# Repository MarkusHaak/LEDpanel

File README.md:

# LEDpanel
A multifunctional, bluetooth controlled LED panel for illuminating 96-well microtiter plates containing biological or chemical samples. The first version of this hardware was developed as part of the iGEM project from team Bielefeld CeBiTec 2017. For a detailed description of this first model and its applications in our project, see the [Hardware page](2017.igem.org/Team:Bielefeld-CeBiTec/Hardware) of our project wiki.

## Disclaimer

The hardware described on this github repository is still in prototype phase and both software and hardware may contain design faults. Furthermore, I do not take any responsibility and I am not liable for any damage that is caused by handling of electrical components or devices based on designs, instructions and information in this repository.

## Some Hints for Assembly

This repository is new and there is a lack of documentation. Until I find the time to write a comprehensive instruction for assembly and usage, the following hints are intended to give some orientation.

* In principal, any LEDs can be mounted on the LED panel. The constant current flowing through the LEDs is adjustable with potentiometers on the PCB itself. The LED panel is designed to be configurable to either control the current of all LEDs with a single potentiometer, or two groups of LEDs with an individual potentiometer for each group. Therefore, it is possible to mount two different groups of LEDs on the LED panel. In any case, I highly recommend to adapt the footprint in the PCB design files according to the instructions in the LED's technical sheets.

* Please adapt the file "model_slim_microtiter_adapter.stl" to fit the micro titer plates that are used in your laboratory.

* The parts list is outdated and is probably missing some required parts. Anyways, it might give some orientation in choosing the right parts.

* The LED panel requires two different voltages supplied over a micro usb cable: 3.3 V for the micro controller and logic, and a seperate LED supply voltage that should be at least 0.4 volts above the supply voltage of the LEDs in use. I used two LM2596 based DC-DC voltage regulator boards in a seperate 3d printed case (voltage_regulators_case.stl) to supply the required voltages from a standard 5V DC mains adapter with a barrel connector.

* The LED panel is intended to be controlled over bluetooth via an Android application. Nevertheless, some gpio pins of the teensy are traced to the side of the PCB for optional soldering of pin headers to the PCB that allow the connection of a small LCD screen and a rotary encoder to control basic functionalities of the LED panel. If this is intended, the Arduino code will probably need to be revised. In addition, the 3d printed case needs to be modified accordingly to create space for the display and the rotary encoder.

* The supplied .stl files are solely for illumination of micro titer plates from beneath. For illumination from above a plate, a different 3d printed microtiter adapter needs to be designed.

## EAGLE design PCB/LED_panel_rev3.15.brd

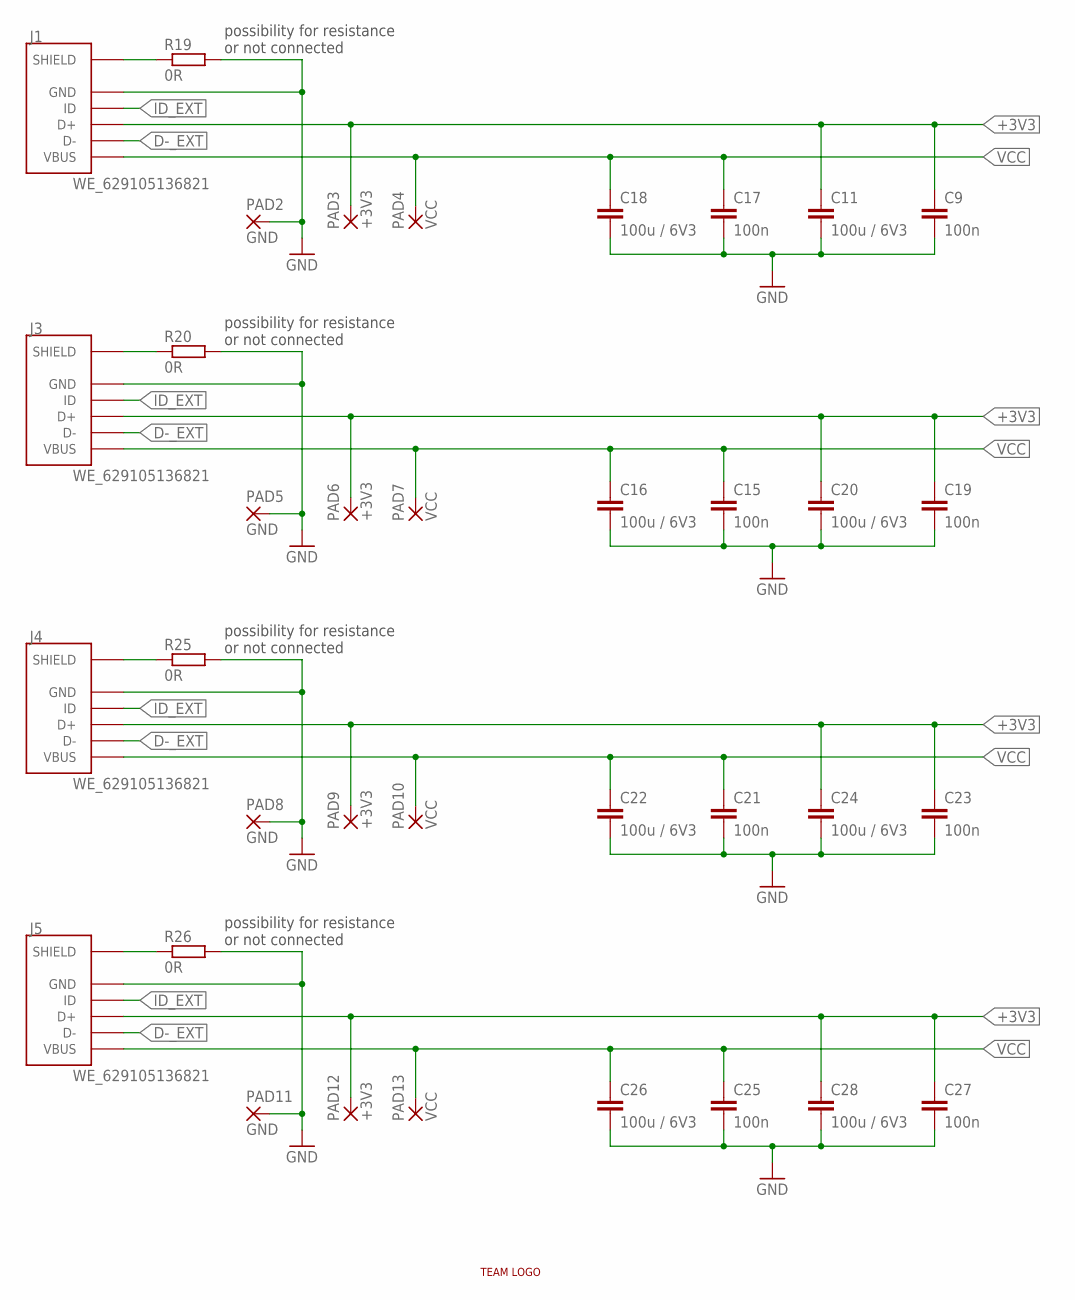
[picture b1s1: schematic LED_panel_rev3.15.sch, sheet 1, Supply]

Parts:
C9, C15, C17, C19, C21, C23, C25, C27: 100n; C1206K
C11, C16, C18, C20, C22, C24, C26, C28: 100u / 6V3; C1206K
J1, J3, J4, J5: WE_629105136821; 629105136821
PAD2, PAD5, PAD8, PAD11: GND; 2,54/1,0
PAD3, PAD6, PAD9, PAD12: +3V3; 2,54/1,0
PAD4, PAD7, PAD10, PAD13: VCC; 2,54/1,0
R19, R20, R25, R26: 0R; R1206
U$99: LOGO_RESTRICT

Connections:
+3V3: C9.1, C11.1, C19.1, C20.1, C23.1, C24.1, C27.1, C28.1, J1.3 (D+), J3.3 (D+), J4.3 (D+), J5.3 (D+), PAD3.1, PAD6.1, PAD9.1, PAD12.1; also elsewhere on the board
D-_EXT: J1.2 (D-), J3.2 (D-), J4.2 (D-), J5.2 (D-); also elsewhere on the board
GND: C9.2, C11.2, C15.2, C16.2, C17.2, C18.2, C19.2, C20.2, C21.2, C22.2, C23.2, C24.2, C25.2, C26.2, C27.2, C28.2, J1.5 (GND), J3.5 (GND), J4.5 (GND), J5.5 (GND), PAD2.1, PAD5.1, PAD8.1, PAD11.1, R19.2, R20.2, R25.2, R26.2; also elsewhere on the board
ID_EXT: J1.4 (ID), J3.4 (ID), J4.4 (ID), J5.4 (ID); also elsewhere on the board
SHIELD1: J1.6 (SHIELD), J1.7 (SHIELD), J1.8 (SHIELD), J1.9 (SHIELD), R19.1
SHIELD3: J3.6 (SHIELD), J3.7 (SHIELD), J3.8 (SHIELD), J3.9 (SHIELD), R20.1
SHIELD4: J4.6 (SHIELD), J4.7 (SHIELD), J4.8 (SHIELD), J4.9 (SHIELD), R25.1
SHIELD5: J5.6 (SHIELD), J5.7 (SHIELD), J5.8 (SHIELD), J5.9 (SHIELD), R26.1
VCC: C15.1, C16.1, C17.1, C18.1, C21.1, C22.1, C25.1, C26.1, J1.1 (VBUS), J3.1 (VBUS), J4.1 (VBUS), J5.1 (VBUS), PAD4.1, PAD7.1, PAD10.1, PAD13.1; also elsewhere on the board

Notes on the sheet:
possibility for resistance or not connected

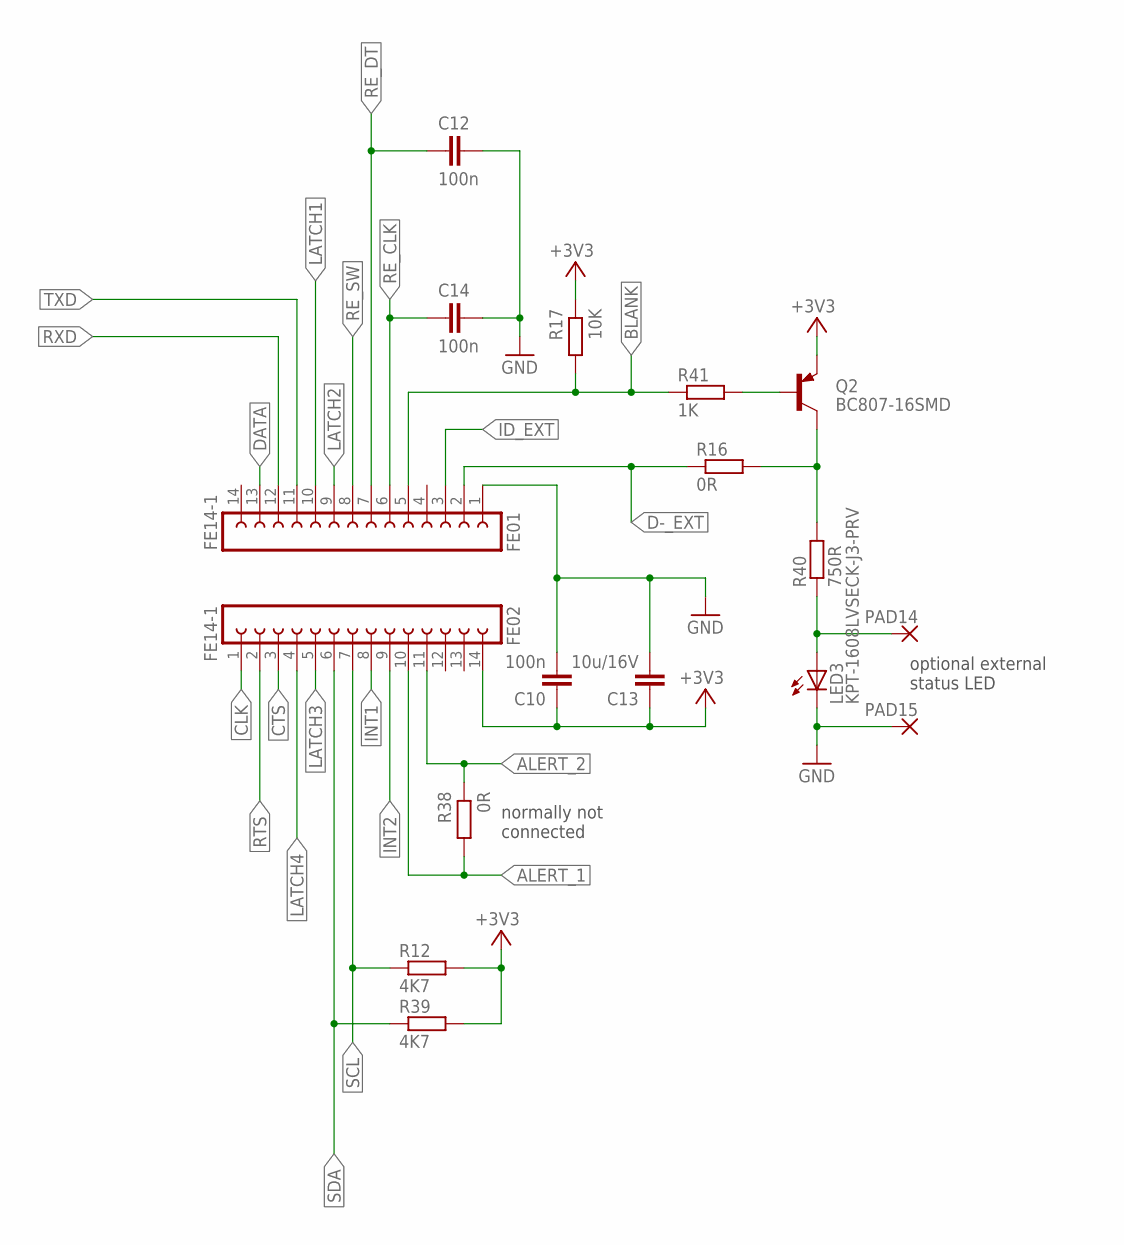
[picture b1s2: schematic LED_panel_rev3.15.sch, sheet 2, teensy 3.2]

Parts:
C10, C12, C14: 100n; C1206K
C13: 10u/16V; C1206K
FE01, FE02: FE14-1; FE14
LED3: KPT-1608LVSECK-J3-PRV; MH_KINGBRIGHT_1.6X0.8
PAD14, PAD15: 2,54/1,0
Q2: BC807-16SMD; SOT23-BEC
R12, R39: 4K7; R1206
R16, R38: 0R; R1206
R17: 10K; R1206
R40: 750R; R1206
R41: 1K; R1206

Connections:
+3V3: C10.1, C13.1, FE02.14, Q2.E, R12.2, R17.1, R39.2; also elsewhere on the board
ALERT_1: FE02.10, R38.2; also elsewhere on the board
ALERT_2: FE02.11, R38.1; also elsewhere on the board
BLANK: FE01.5, R17.2, R41.1; also elsewhere on the board
CLK: FE02.1; also elsewhere on the board
CTS: FE02.3; also elsewhere on the board
D-_EXT: FE01.2, R16.1; also elsewhere on the board
DATA: FE01.13; also elsewhere on the board
GND: C10.2, C12.1, C13.2, C14.1, FE01.1, LED3.C, PAD15.1; also elsewhere on the board
ID_EXT: FE01.3; also elsewhere on the board
INT1: FE02.8; also elsewhere on the board
INT2: FE02.9; also elsewhere on the board
LATCH1: FE01.10; also elsewhere on the board
LATCH2: FE01.9; also elsewhere on the board
LATCH3: FE02.5; also elsewhere on the board
LATCH4: FE02.4; also elsewhere on the board
unnamed: Q2.B, R41.2
unnamed: Q2.C, R16.2, R40.2
unnamed: LED3.A, PAD14.1, R40.1
RE_CLK: C14.2, FE01.6; also elsewhere on the board
RE_DT: C12.2, FE01.7; also elsewhere on the board
RE_SW: FE01.8; also elsewhere on the board
RTS: FE02.2; also elsewhere on the board
RXD: FE01.12; also elsewhere on the board
SCL: FE02.7, R12.1; also elsewhere on the board
SDA: FE02.6, R39.1; also elsewhere on the board
TXD: FE01.11; also elsewhere on the board

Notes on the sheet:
normally not connected
optional external status LED

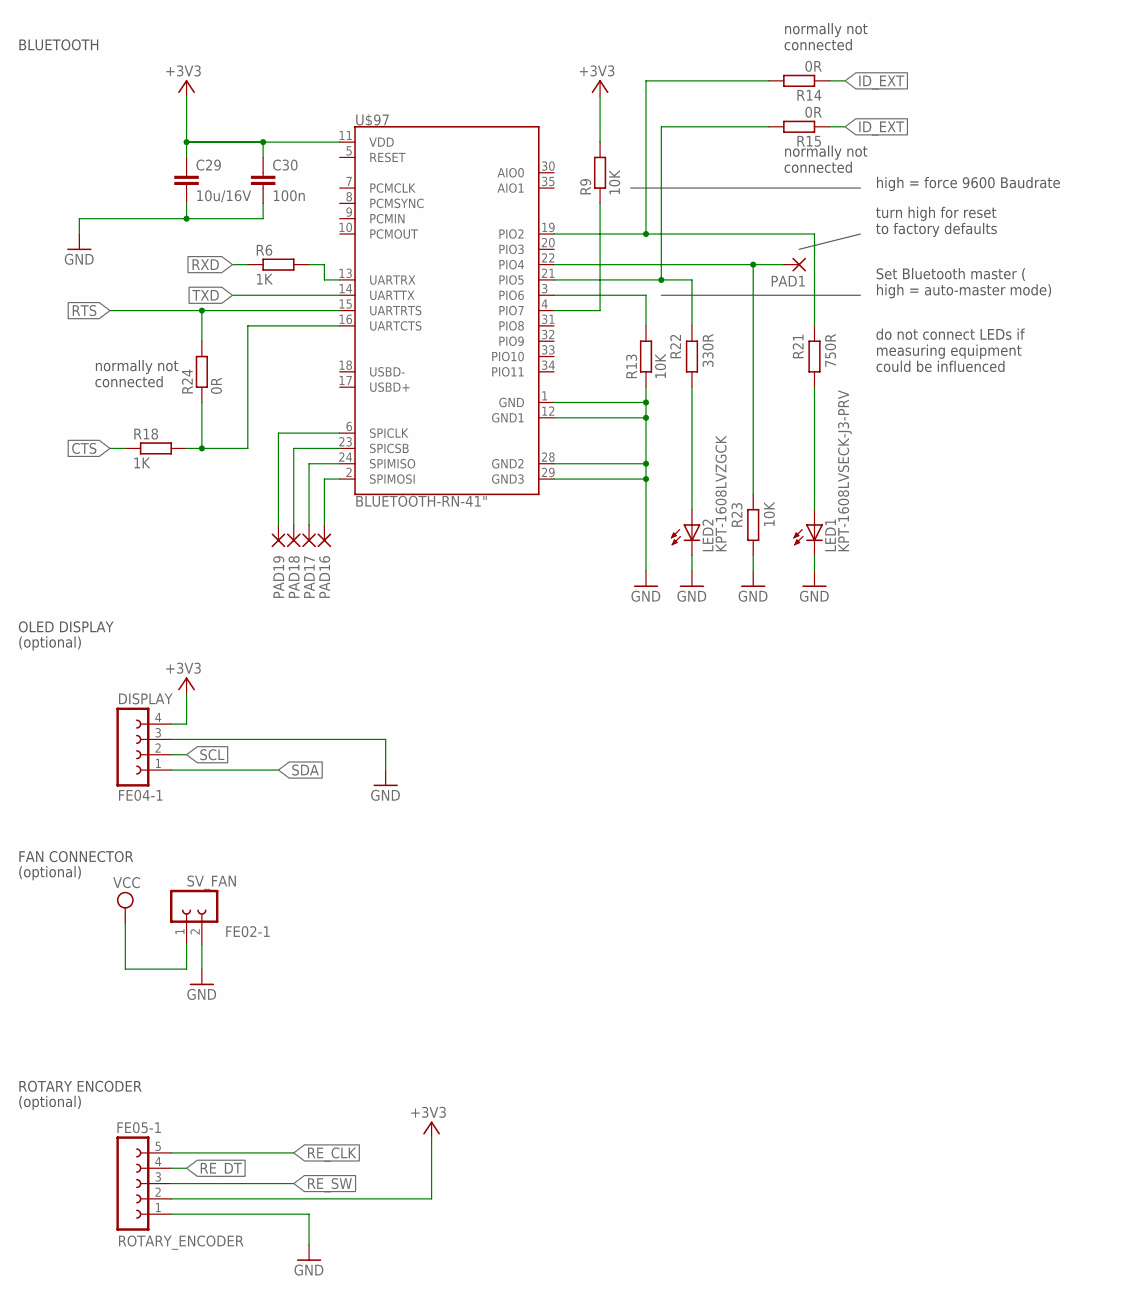
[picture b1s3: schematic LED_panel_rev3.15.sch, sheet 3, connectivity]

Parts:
C29: 10u/16V; C1206K
C30: 100n; C1206K
DISPLAY: FE04-1; FE04
LED1: KPT-1608LVSECK-J3-PRV; MH_KINGBRIGHT_1.6X0.8
LED2: KPT-1608LVZGCK; MH_KINGBRIGHT_1.6X0.8
PAD1, PAD16, PAD17, PAD18, PAD19: 2,54/1,0
R6, R18: 1K; R1206
R9, R13, R23: 10K; R1206
R14, R15, R24: 0R; R1206
R21: 750R; R1206
R22: 330R; R1206
ROTARY_ENCODER: FE05-1; FE05
SV_FAN: FE02-1; FE02
U$97: BLUETOOTH-RN-41"; RN41

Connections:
+3V3: C29.1, C30.1, DISPLAY.4, R9.2, ROTARY_ENCODER.2, U$97.11 (VDD); also elsewhere on the board
CTS: R18.1; also elsewhere on the board
GND: C29.2, C30.2, DISPLAY.3, LED1.C, LED2.C, R13.1, R23.2, ROTARY_ENCODER.1, SV_FAN.2, U$97.1 (GND), U$97.12 (GND1), U$97.28 (GND2), U$97.29 (GND3); also elsewhere on the board
ID_EXT: R14.1, R15.1; also elsewhere on the board
unnamed: R9.1, U$97.4 (PIO7)
unnamed: R13.2, U$97.3 (PIO6)
unnamed: R18.2, R24.1, U$97.16 (UARTCTS)
unnamed: PAD16.1, U$97.2 (SPIMOSI)
unnamed: PAD17.1, U$97.24 (SPIMISO)
unnamed: R6.2, U$97.13 (UARTRX)
unnamed: PAD18.1, U$97.23 (SPICSB)
unnamed: R15.2, R22.1, U$97.21 (PIO5)
unnamed: LED2.A, R22.2
unnamed: PAD19.1, U$97.6 (SPICLK)
unnamed: LED1.A, R21.2
unnamed: R14.2, R21.1, U$97.19 (PIO2)
PIO4: PAD1.1, R23.1, U$97.22 (PIO4)
RE_CLK: ROTARY_ENCODER.5; also elsewhere on the board
RE_DT: ROTARY_ENCODER.4; also elsewhere on the board
RE_SW: ROTARY_ENCODER.3; also elsewhere on the board
RTS: R24.2, U$97.15 (UARTRTS); also elsewhere on the board
RXD: R6.1; also elsewhere on the board
SCL: DISPLAY.2; also elsewhere on the board
SDA: DISPLAY.1; also elsewhere on the board
TXD: U$97.14 (UARTTX); also elsewhere on the board
VCC: SV_FAN.1; also elsewhere on the board

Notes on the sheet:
normally not connected
OLED DISPLAY
ROTARY ENCODER
BLUETOOTH
FAN CONNECTOR
do not connect LEDs if measuring equipment could be influenced
(optional)
high = force 9600 Baudrate
turn high for reset to factory defaults
Set Bluetooth master ( high = auto-master mode)

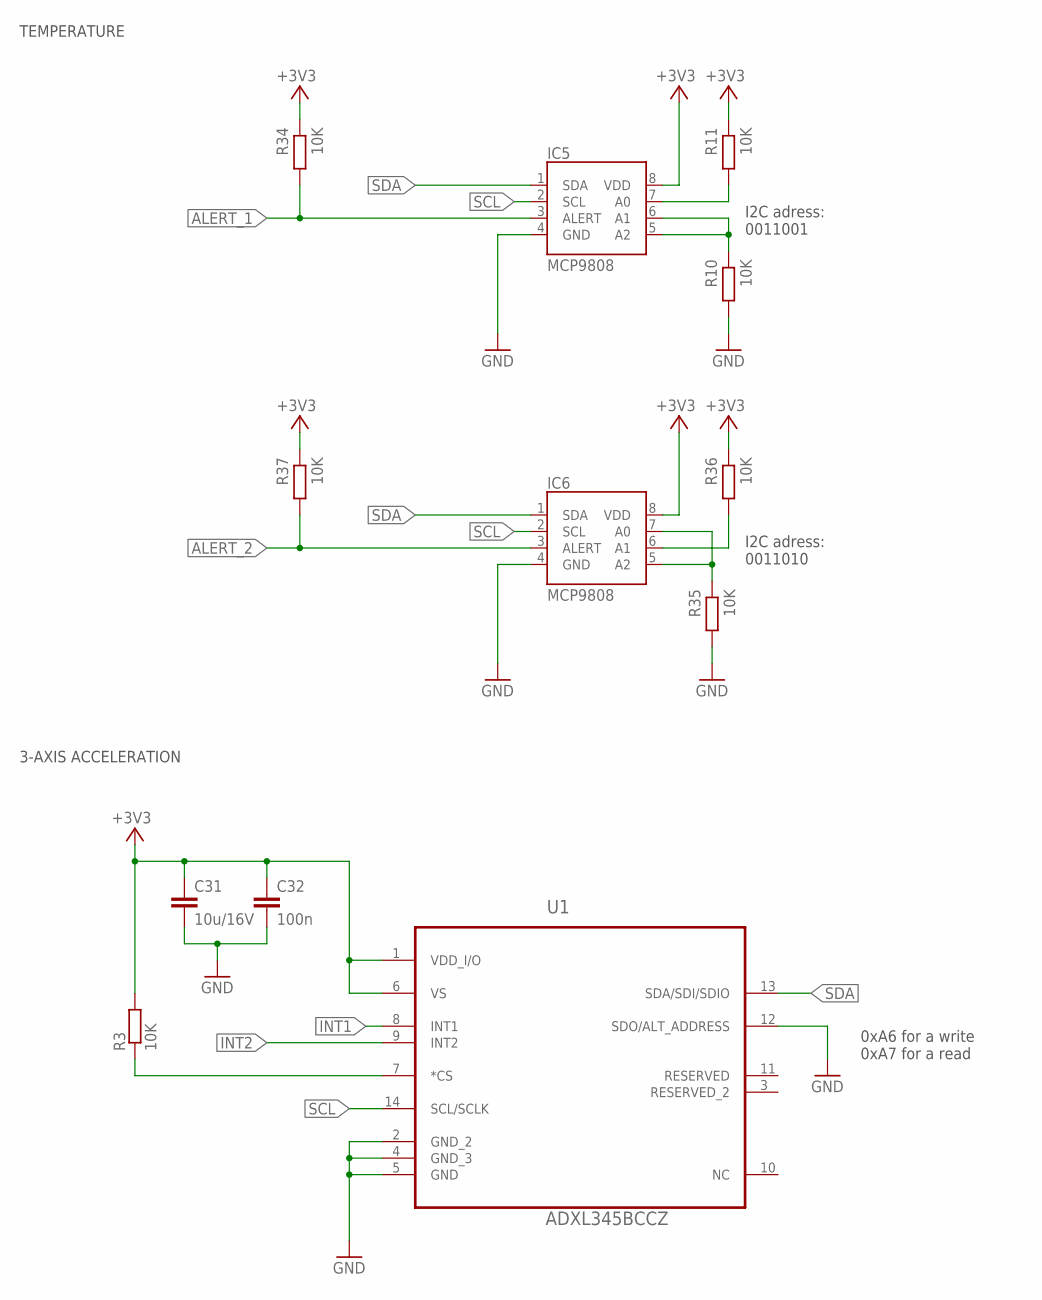
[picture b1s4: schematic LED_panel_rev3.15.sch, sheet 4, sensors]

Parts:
C31: 10u/16V; C1206K
C32: 100n; C1206K
IC5, IC6: MCP9808; MSOP8
R3, R10, R11, R34, R35, R36, R37: 10K; R1206
U1: ADXL345BCCZ; LGA14R80P3X6_300X500X100

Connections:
+3V3: C31.1, C32.1, IC5.8 (VDD), IC6.8 (VDD), R3.2, R11.1, R34.1, R36.1, R37.1, U1.1 (VDD_I/O), U1.6 (VS); also elsewhere on the board
ALERT_1: IC5.3 (ALERT), R34.2; also elsewhere on the board
ALERT_2: IC6.3 (ALERT), R37.2; also elsewhere on the board
GND: C31.2, C32.2, IC5.4 (GND), IC6.4 (GND), R10.2, R35.2, U1.2 (GND_2), U1.4 (GND_3), U1.5 (GND), U1.12 (SDO/ALT_ADDRESS); also elsewhere on the board
INT1: U1.8 (INT1); also elsewhere on the board
INT2: U1.9 (INT2); also elsewhere on the board
unnamed: IC5.5 (A2), IC5.6 (A1), R10.1
unnamed: IC5.7 (A0), R11.2
unnamed: IC6.5 (A2), IC6.7 (A0), R35.1
unnamed: R3.1, U1.7 (*CS)
unnamed: IC6.6 (A1), R36.2
SCL: IC5.2 (SCL), IC6.2 (SCL), U1.14 (SCL/SCLK); also elsewhere on the board
SDA: IC5.1 (SDA), IC6.1 (SDA), U1.13 (SDA/SDI/SDIO); also elsewhere on the board

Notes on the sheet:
TEMPERATURE
I2C adress: 0011001
I2C adress: 0011010
3-AXIS ACCELERATION
0xA6 for a write 0xA7 for a read

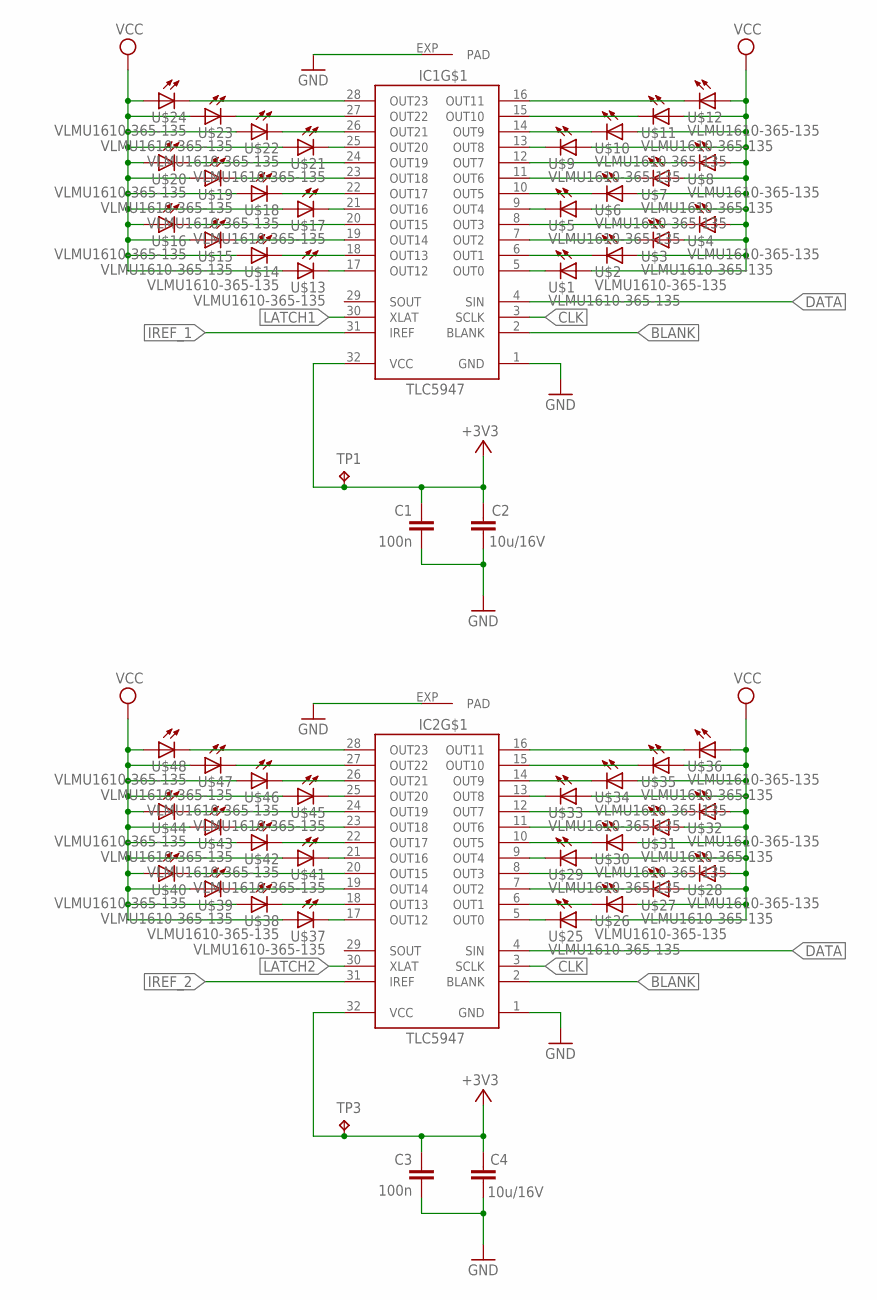
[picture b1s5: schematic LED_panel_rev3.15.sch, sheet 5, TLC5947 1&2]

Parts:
C1, C3: 100n; C1206K
C2, C4: 10u/16V; C1206K
IC1, IC2: TLC5947-DAP; HTSSOP32DAP
TP1, TP3: TPTP20R; TP20R
U$1, U$2, U$3, U$4, U$5, U$6, U$7, U$8, U$9, U$10, U$11, U$12, U$13, U$14, U$15, U$16, U$17, U$18, U$19, U$20, U$21, U$22, U$23, U$24, U$25, U$26, U$27, U$28, U$29, U$30, U$31, U$32, U$33, U$34, U$35, U$36, U$37, U$38, U$39, U$40, U$41, U$42, U$43, U$44, U$45, U$46, U$47, U$48: VLMU1610-365-135; SMD_CERAMIC_MID_POWER

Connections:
+3V3: C1.2, C2.2, C3.2, C4.2, IC1.32 (VCC), IC2.32 (VCC), TP1.TP, TP3.TP; also elsewhere on the board
BLANK: IC1.2 (BLANK), IC2.2 (BLANK); also elsewhere on the board
CLK: IC1.3 (SCLK), IC2.3 (SCLK); also elsewhere on the board
DATA: IC1.4 (SIN), IC2.4 (SIN); also elsewhere on the board
GND: C1.1, C2.1, C3.1, C4.1, IC1.1 (GND), IC1.EXP (PAD), IC2.1 (GND), IC2.EXP (PAD); also elsewhere on the board
IREF_1: IC1.31 (IREF); also elsewhere on the board
IREF_2: IC2.31 (IREF); also elsewhere on the board
LATCH1: IC1.30 (XLAT); also elsewhere on the board
LATCH2: IC2.30 (XLAT); also elsewhere on the board
unnamed: IC1.28 (OUT23), U$24.P$2 (C)
unnamed: IC1.27 (OUT22), U$23.P$2 (C)
unnamed: IC1.26 (OUT21), U$22.P$2 (C)
unnamed: IC1.25 (OUT20), U$21.P$2 (C)
unnamed: IC1.24 (OUT19), U$20.P$2 (C)
unnamed: IC1.23 (OUT18), U$19.P$2 (C)
unnamed: IC1.22 (OUT17), U$18.P$2 (C)
unnamed: IC1.21 (OUT16), U$17.P$2 (C)
unnamed: IC1.20 (OUT15), U$16.P$2 (C)
unnamed: IC1.19 (OUT14), U$15.P$2 (C)
unnamed: IC1.18 (OUT13), U$14.P$2 (C)
unnamed: IC1.17 (OUT12), U$13.P$2 (C)
unnamed: IC1.16 (OUT11), U$12.P$2 (C)
unnamed: IC1.15 (OUT10), U$11.P$2 (C)
unnamed: IC1.14 (OUT9), U$10.P$2 (C)
unnamed: IC1.13 (OUT8), U$9.P$2 (C)
unnamed: IC1.12 (OUT7), U$8.P$2 (C)
unnamed: IC2.28 (OUT23), U$48.P$2 (C)
unnamed: IC2.27 (OUT22), U$47.P$2 (C)
unnamed: IC1.11 (OUT6), U$7.P$2 (C)
unnamed: IC2.26 (OUT21), U$46.P$2 (C)
unnamed: IC1.10 (OUT5), U$6.P$2 (C)
unnamed: IC2.25 (OUT20), U$45.P$2 (C)
unnamed: IC1.9 (OUT4), U$5.P$2 (C)
unnamed: IC2.24 (OUT19), U$44.P$2 (C)
unnamed: IC1.8 (OUT3), U$4.P$2 (C)
unnamed: IC2.23 (OUT18), U$43.P$2 (C)
unnamed: IC1.7 (OUT2), U$3.P$2 (C)
unnamed: IC2.22 (OUT17), U$42.P$2 (C)
unnamed: IC1.6 (OUT1), U$2.P$2 (C)
unnamed: IC2.21 (OUT16), U$41.P$2 (C)
unnamed: IC1.5 (OUT0), U$1.P$2 (C)
unnamed: IC2.20 (OUT15), U$40.P$2 (C)
unnamed: IC2.19 (OUT14), U$39.P$2 (C)
unnamed: IC2.18 (OUT13), U$38.P$2 (C)
unnamed: IC2.17 (OUT12), U$37.P$2 (C)
unnamed: IC2.16 (OUT11), U$36.P$2 (C)
unnamed: IC2.15 (OUT10), U$35.P$2 (C)
unnamed: IC2.14 (OUT9), U$34.P$2 (C)
unnamed: IC2.13 (OUT8), U$33.P$2 (C)
unnamed: IC2.12 (OUT7), U$32.P$2 (C)
unnamed: IC2.11 (OUT6), U$31.P$2 (C)
unnamed: IC2.10 (OUT5), U$30.P$2 (C)
unnamed: IC2.9 (OUT4), U$29.P$2 (C)
unnamed: IC2.8 (OUT3), U$28.P$2 (C)
unnamed: IC2.7 (OUT2), U$27.P$2 (C)
unnamed: IC2.6 (OUT1), U$26.P$2 (C)
unnamed: IC2.5 (OUT0), U$25.P$2 (C)
VCC: U$1.P$1 (A), U$2.P$1 (A), U$3.P$1 (A), U$4.P$1 (A), U$5.P$1 (A), U$6.P$1 (A), U$7.P$1 (A), U$8.P$1 (A), U$9.P$1 (A), U$10.P$1 (A), U$11.P$1 (A), U$12.P$1 (A), U$13.P$1 (A), U$14.P$1 (A), U$15.P$1 (A), U$16.P$1 (A), U$17.P$1 (A), U$18.P$1 (A), U$19.P$1 (A), U$20.P$1 (A), U$21.P$1 (A), U$22.P$1 (A), U$23.P$1 (A), U$24.P$1 (A), U$25.P$1 (A), U$26.P$1 (A), U$27.P$1 (A), U$28.P$1 (A), U$29.P$1 (A), U$30.P$1 (A), U$31.P$1 (A), U$32.P$1 (A), U$33.P$1 (A), U$34.P$1 (A), U$35.P$1 (A), U$36.P$1 (A), U$37.P$1 (A), U$38.P$1 (A), U$39.P$1 (A), U$40.P$1 (A), U$41.P$1 (A), U$42.P$1 (A), U$43.P$1 (A), U$44.P$1 (A), U$45.P$1 (A), U$46.P$1 (A), U$47.P$1 (A), U$48.P$1 (A); also elsewhere on the board

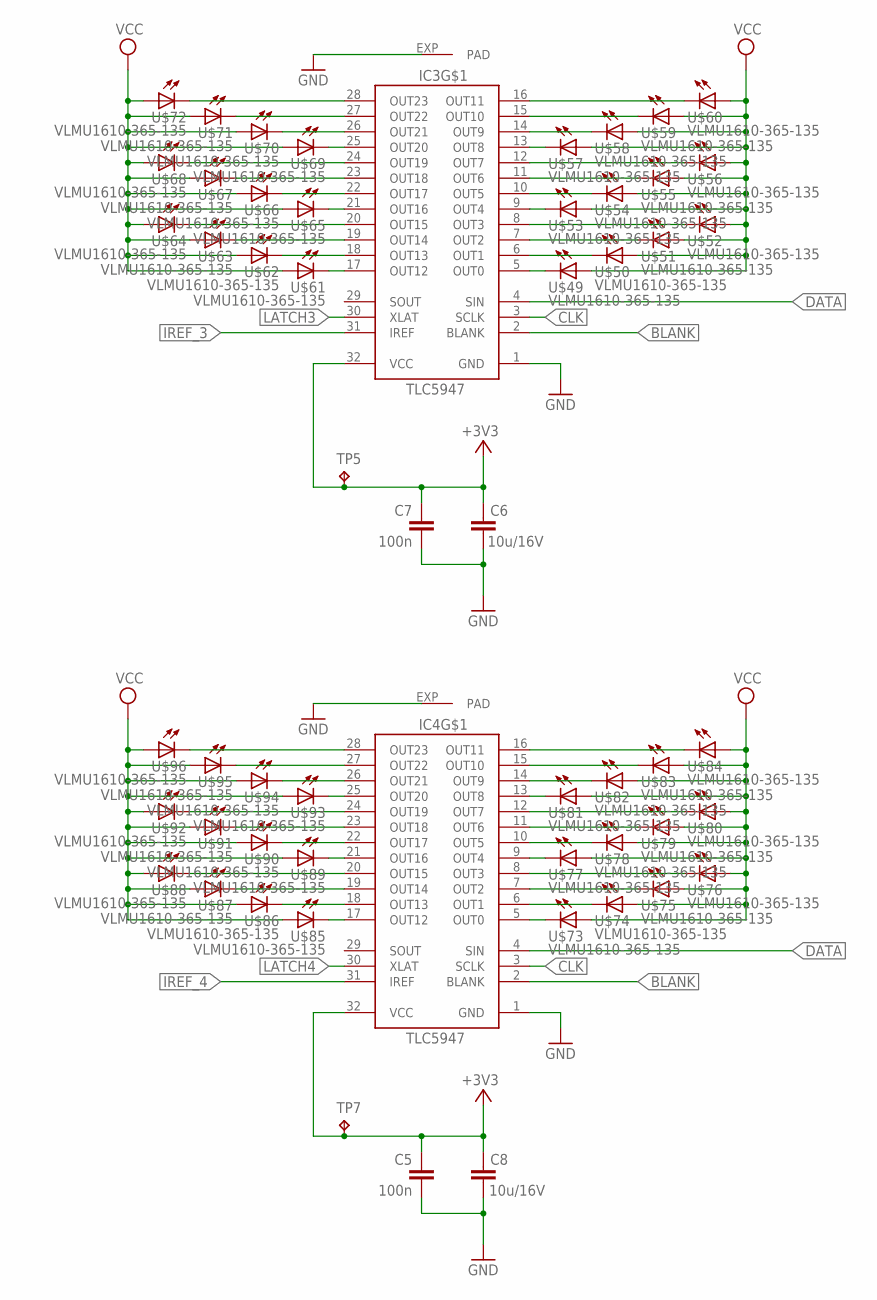
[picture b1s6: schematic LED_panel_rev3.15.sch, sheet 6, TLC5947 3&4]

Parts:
C5, C7: 100n; C1206K
C6, C8: 10u/16V; C1206K
IC3, IC4: TLC5947-DAP; HTSSOP32DAP
TP5, TP7: TPTP20R; TP20R
U$49, U$50, U$51, U$52, U$53, U$54, U$55, U$56, U$57, U$58, U$59, U$60, U$61, U$62, U$63, U$64, U$65, U$66, U$67, U$68, U$69, U$70, U$71, U$72, U$73, U$74, U$75, U$76, U$77, U$78, U$79, U$80, U$81, U$82, U$83, U$84, U$85, U$86, U$87, U$88, U$89, U$90, U$91, U$92, U$93, U$94, U$95, U$96: VLMU1610-365-135; SMD_CERAMIC_MID_POWER

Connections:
+3V3: C5.2, C6.2, C7.2, C8.2, IC3.32 (VCC), IC4.32 (VCC), TP5.TP, TP7.TP; also elsewhere on the board
BLANK: IC3.2 (BLANK), IC4.2 (BLANK); also elsewhere on the board
CLK: IC3.3 (SCLK), IC4.3 (SCLK); also elsewhere on the board
DATA: IC3.4 (SIN), IC4.4 (SIN); also elsewhere on the board
GND: C5.1, C6.1, C7.1, C8.1, IC3.1 (GND), IC3.EXP (PAD), IC4.1 (GND), IC4.EXP (PAD); also elsewhere on the board
IREF_3: IC3.31 (IREF); also elsewhere on the board
IREF_4: IC4.31 (IREF); also elsewhere on the board
LATCH3: IC3.30 (XLAT); also elsewhere on the board
LATCH4: IC4.30 (XLAT); also elsewhere on the board
unnamed: IC3.28 (OUT23), U$72.P$2 (C)
unnamed: IC3.27 (OUT22), U$71.P$2 (C)
unnamed: IC3.26 (OUT21), U$70.P$2 (C)
unnamed: IC3.25 (OUT20), U$69.P$2 (C)
unnamed: IC3.24 (OUT19), U$68.P$2 (C)
unnamed: IC3.23 (OUT18), U$67.P$2 (C)
unnamed: IC3.22 (OUT17), U$66.P$2 (C)
unnamed: IC3.21 (OUT16), U$65.P$2 (C)
unnamed: IC3.20 (OUT15), U$64.P$2 (C)
unnamed: IC3.19 (OUT14), U$63.P$2 (C)
unnamed: IC3.18 (OUT13), U$62.P$2 (C)
unnamed: IC3.17 (OUT12), U$61.P$2 (C)
unnamed: IC3.16 (OUT11), U$60.P$2 (C)
unnamed: IC3.15 (OUT10), U$59.P$2 (C)
unnamed: IC3.14 (OUT9), U$58.P$2 (C)
unnamed: IC3.13 (OUT8), U$57.P$2 (C)
unnamed: IC3.12 (OUT7), U$56.P$2 (C)
unnamed: IC3.11 (OUT6), U$55.P$2 (C)
unnamed: IC3.10 (OUT5), U$54.P$2 (C)
unnamed: IC3.9 (OUT4), U$53.P$2 (C)
unnamed: IC3.8 (OUT3), U$52.P$2 (C)
unnamed: IC3.7 (OUT2), U$51.P$2 (C)
unnamed: IC3.6 (OUT1), U$50.P$2 (C)
unnamed: IC3.5 (OUT0), U$49.P$2 (C)
unnamed: IC4.28 (OUT23), U$96.P$2 (C)
unnamed: IC4.27 (OUT22), U$95.P$2 (C)
unnamed: IC4.26 (OUT21), U$94.P$2 (C)
unnamed: IC4.25 (OUT20), U$93.P$2 (C)
unnamed: IC4.24 (OUT19), U$92.P$2 (C)
unnamed: IC4.23 (OUT18), U$91.P$2 (C)
unnamed: IC4.22 (OUT17), U$90.P$2 (C)
unnamed: IC4.21 (OUT16), U$89.P$2 (C)
unnamed: IC4.20 (OUT15), U$88.P$2 (C)
unnamed: IC4.19 (OUT14), U$87.P$2 (C)
unnamed: IC4.18 (OUT13), U$86.P$2 (C)
unnamed: IC4.17 (OUT12), U$85.P$2 (C)
unnamed: IC4.16 (OUT11), U$84.P$2 (C)
unnamed: IC4.15 (OUT10), U$83.P$2 (C)
unnamed: IC4.14 (OUT9), U$82.P$2 (C)
unnamed: IC4.13 (OUT8), U$81.P$2 (C)
unnamed: IC4.12 (OUT7), U$80.P$2 (C)
unnamed: IC4.11 (OUT6), U$79.P$2 (C)
unnamed: IC4.10 (OUT5), U$78.P$2 (C)
unnamed: IC4.9 (OUT4), U$77.P$2 (C)
unnamed: IC4.8 (OUT3), U$76.P$2 (C)
unnamed: IC4.7 (OUT2), U$75.P$2 (C)
unnamed: IC4.6 (OUT1), U$74.P$2 (C)
unnamed: IC4.5 (OUT0), U$73.P$2 (C)
VCC: U$49.P$1 (A), U$50.P$1 (A), U$51.P$1 (A), U$52.P$1 (A), U$53.P$1 (A), U$54.P$1 (A), U$55.P$1 (A), U$56.P$1 (A), U$57.P$1 (A), U$58.P$1 (A), U$59.P$1 (A), U$60.P$1 (A), U$61.P$1 (A), U$62.P$1 (A), U$63.P$1 (A), U$64.P$1 (A), U$65.P$1 (A), U$66.P$1 (A), U$67.P$1 (A), U$68.P$1 (A), U$69.P$1 (A), U$70.P$1 (A), U$71.P$1 (A), U$72.P$1 (A), U$73.P$1 (A), U$74.P$1 (A), U$75.P$1 (A), U$76.P$1 (A), U$77.P$1 (A), U$78.P$1 (A), U$79.P$1 (A), U$80.P$1 (A), U$81.P$1 (A), U$82.P$1 (A), U$83.P$1 (A), U$84.P$1 (A), U$85.P$1 (A), U$86.P$1 (A), U$87.P$1 (A), U$88.P$1 (A), U$89.P$1 (A), U$90.P$1 (A), U$91.P$1 (A), U$92.P$1 (A), U$93.P$1 (A), U$94.P$1 (A), U$95.P$1 (A), U$96.P$1 (A); also elsewhere on the board

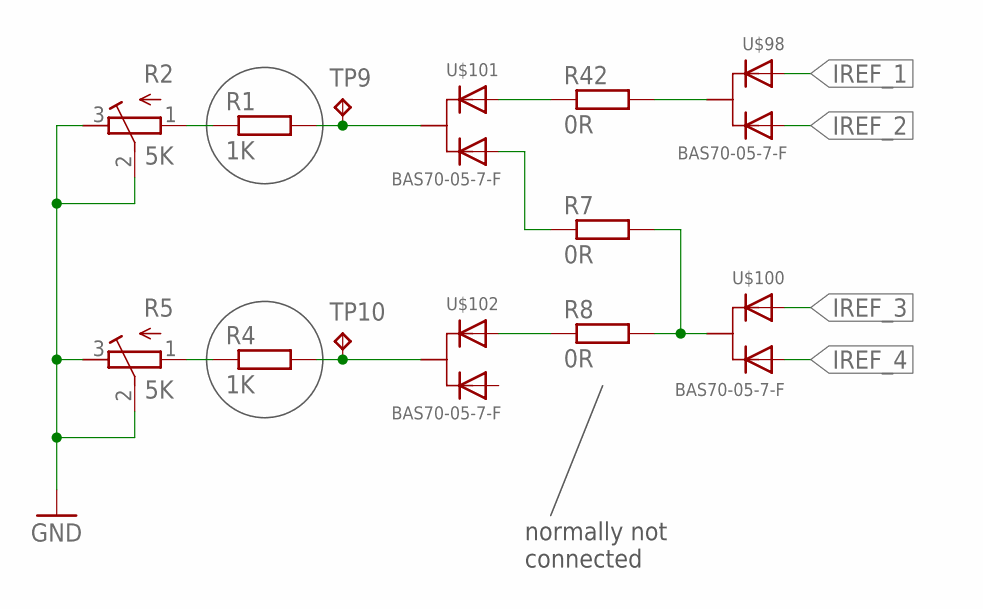
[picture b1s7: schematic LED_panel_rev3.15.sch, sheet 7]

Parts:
R1, R4: 1K; R1206
R2, R5: 5K; RTRIM4G/J
R7, R8, R42: 0R; R1206
TP9, TP10: TPTP20R; TP20R
U$98, U$100, U$101, U$102: BAS70-05-7-F; SOT23

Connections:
GND: R2.2 (S), R2.3 (E), R5.2 (S), R5.3 (E); also elsewhere on the board
IREF_1: U$98.2 (B); also elsewhere on the board
IREF_1&2: R42.2, U$98.3 (C)
IREF_2: U$98.1 (A); also elsewhere on the board
IREF_3: U$100.2 (B); also elsewhere on the board
IREF_3&4: R7.2, R8.2, U$100.3 (C)
IREF_4: U$100.1 (A); also elsewhere on the board
unnamed: R1.1, R2.1 (A)
unnamed: R4.1, R5.1 (A)
unnamed: R1.2, TP9.TP, U$101.3 (C)
unnamed: R4.2, TP10.TP, U$102.3 (C)
unnamed: R42.1, U$101.2 (B)
unnamed: R7.1, U$101.1 (A)
unnamed: R8.1, U$102.2 (B)

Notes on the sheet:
normally not connected

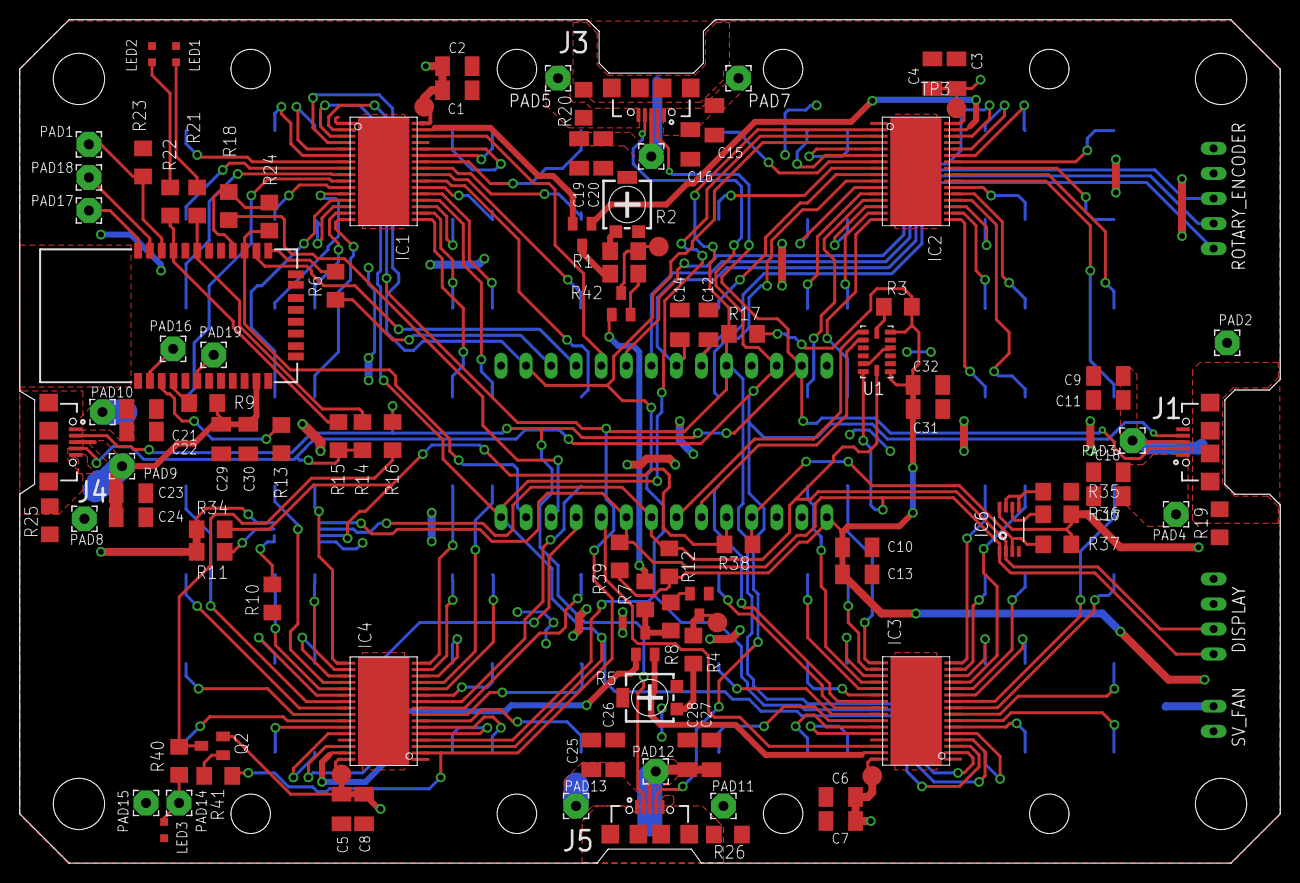
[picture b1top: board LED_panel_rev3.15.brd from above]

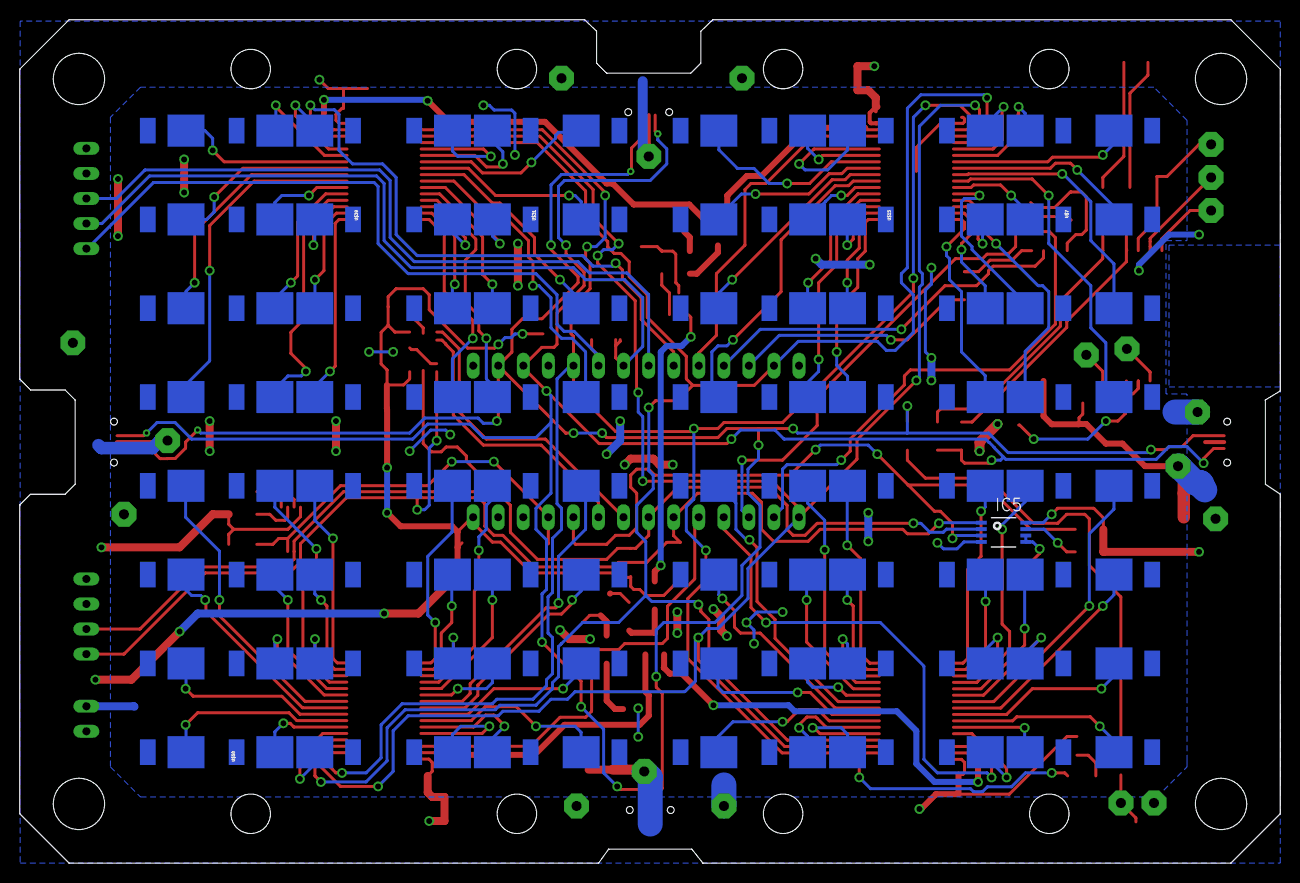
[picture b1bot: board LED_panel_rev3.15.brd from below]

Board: 2 copper layers, 127.8 x 85.5 mm, 214 parts (97 on the bottom side), 159 nets.

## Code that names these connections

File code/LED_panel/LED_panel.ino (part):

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#include <Adafruit_ADXL345_U.h>

// rotary encoder
#define RE_CLK 4 //2
#define RE_DT 5//4
#define RE_SW 6

// HC-05/HC-06 bluetooth module
#define TXD 9
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#define OLED_RESET 2 // nicht genutzt bei diesem Display

//others
#define BLANK	 	3

// iGEM Bielefeld-CeBiTec 2017 logo
const uint8_t logo[8129] PROGMEM = {
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	blank_state = 1;

	// rotary encoder setup
	pinMode(RE_SW, INPUT);
	pinMode(RE_CLK, INPUT);
	pinMode(RE_DT, INPUT);
	attachInterrupt(digitalPinToInterrupt(RE_CLK), irupt_re_clk, CHANGE);
	attachInterrupt(digitalPinToInterrupt(RE_SW), irupt_re_sw, CHANGE);
	lst_rot_clk = digitalRead(RE_CLK);
	intensity = 100;
	time_inten = 1;
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
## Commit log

2019-06-07 initial commit with revision 3.15 source files
2019-06-07 modify description
2019-06-07 add hints
